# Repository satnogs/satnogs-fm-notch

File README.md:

# SatNOGS FM Notch filter

FM Notch filter for SatNOGS project.

An FM notch filter is used to reject FM signals 88MHz - 108MHz.
More information about filter in report and qucs project files.

Repository includes all source files for PCB's qucs, simulation files and reports about the filter 
specifications.

## Repository policy
SatNOGS hardware repositories only track source design files. All needed derivative files (e.g. grb etc) 
for production are created per release, packaged in an archive and uploaded linked to a  [release](https://github.com/satnogs/satnogs-fm-notch/releases).

Each major release (x.0.0) is branched out of master. Subsequent fixes (minor or not) are commited on those branches and tagged accordingly.

Master branch is most times under active development, so expect things to break. For production ready and previous releases source files check tags and branches.

## License

Licensed under the [CERN OHLv1.2](LICENSE).

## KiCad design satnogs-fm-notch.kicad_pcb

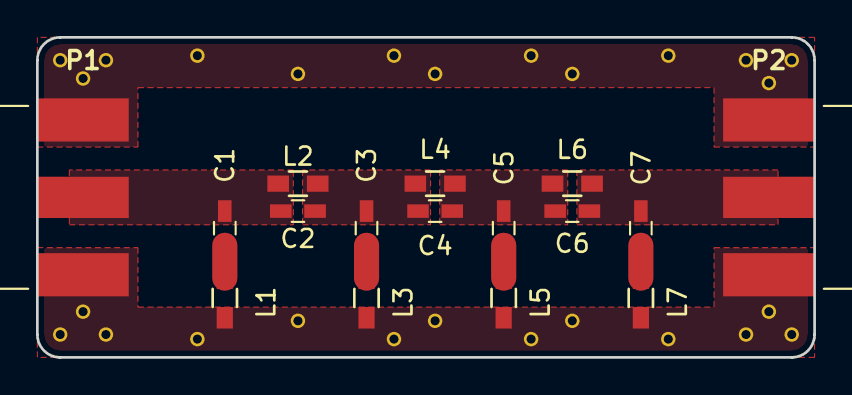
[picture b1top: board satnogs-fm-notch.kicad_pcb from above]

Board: 2 copper layers, 43.2 x 17.8 mm, 16 parts (0 on the bottom side), 9 nets.

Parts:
C1: 6.8p; C_0603_HandSoldering
C2, C4, C6: 100pF; C_0603_HandSoldering
C3, C5: 15pF; C_0603_HandSoldering
C7: 6.8pF; C_0603_HandSoldering
L1, L7: 330nF; R_0603_HandSoldering
L2, L6: 22nH; R_0603_HandSoldering
L3: 180nH; R_0603_HandSoldering
L4: 27nF; R_0603_HandSoldering
L5: 180nF; R_0603_HandSoldering
P1, P2: Conn_RF; Conn_SMA_Molex_73251-1150

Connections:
GND: L1.2, L3.2, L5.2, L7.2, P1.2, P2.2
unnamed: C1.1, C2.2, L2.1, P1.1
unnamed: C1.2, L1.1
unnamed: C2.1, C3.1, C4.2, L2.2, L4.1
unnamed: C3.2, L3.1
unnamed: C4.1, C5.1, C6.2, L4.2, L6.1
unnamed: C5.2, L5.1
unnamed: C6.1, C7.1, L6.2, P2.1
unnamed: C7.2, L7.1

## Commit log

2017-02-27 Add kicad project
2017-02-27 Add qucs project
2017-02-27 Add report about specification of filter
2017-02-27 Update README file

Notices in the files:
satnogs-fm-notch.kicad_pcb:
©Libre Space Foundation
